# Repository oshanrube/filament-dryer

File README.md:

# Filament dryer

3D-printed filament dryer boxes, one per printer: heated to 40-70 °C, weighing the reel and reporting to the Printer Control Center over Wi-Fi. Two versions share the same heater, fans, controller, sensors and 12 V feed, so they use the same spares.

| Version | Folder | What it is |
| --- | --- | --- |
| 2-roll feeder | [`2-roll-feeder/`](2-roll-feeder/) | Two reels and a feeder pod; switches to the second reel automatically when the printer reports a runout |
| 1 roll | [`1-roll/`](1-roll/) | One reel, no feeders; smaller and simpler |
| Dumb (STC-3028) | [`dumb/`](dumb/) | The cheapest box: an STC-3028 humidity + temperature controller and a W1209 switch a 96 W heater in two steps. No microcontroller, scale or Wi-Fi |

**Published plan:** GitHub Pages from `/docs` on `main` (Settings → Pages → Deploy from a branch → `main`, `/docs`). The site has an overview page and one tab per version.

## Layout

| Path | What |
| --- | --- |
| `<version>/page.html` | That version's page content |
| `<version>/bom.csv` | Parts list with AliExpress search terms and approximate prices |
| `<version>/wiring.svg`, `<version>/wiring-table.html` | Wiring diagram and connector table (generated by `tools/gen_wiring.py`) |
| `<version>/images/` | Drawings (1-roll ones generated by `1-roll/tools/gen_drawings.py`) |
| `pcb/` | Controller board for JLCPCB assembly: wired schematic (`pcb/schematic.svg`/`.pdf`), KiCad schematic, JLCPCB BOMs (see `pcb/README.md`) |
| `firmware/` | ESP32-C3 firmware (PlatformIO, like the gate controller): build `dryer-1roll` runs the 1-roll PCB and the perfboard. See `firmware/README.md` |
| `.github/workflows/firmware.yml` | Builds the firmware on a `fw-v*` tag and attaches `dryer-1roll.bin` (OTA) and `dryer-1roll-full.bin` (flash at 0x0) to the release |
| `site/layout.html`, `site/overview.html` | Shared page shell with the tabs, and the overview page |
| `tools/build_site.py` | Builds `docs/` (the published site) from the folders above |
| `docs/` | Generated; don't edit by hand |

## Rebuild

```bash
python3 1-roll/tools/gen_drawings.py && python3 tools/gen_wiring.py && python3 dumb/tools/gen_dumb.py
```

```bash
python3 pcb/tools/gen_kicad.py && python3 pcb/tools/gen_schematic_svg.py && node pcb/tools/svg_to_pdf.js pcb/schematic.svg pcb/schematic.pdf
```

```bash
python3 tools/build_site.py
```

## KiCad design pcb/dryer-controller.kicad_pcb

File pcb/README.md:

# Dryer controller board (JLCPCB assembly)

One controller board for both dryer versions. The 2-roll build fits everything; the 1-roll build leaves the feeder parts off. KiCad 7 project, generated from one table in `tools/gen_kicad.py`.

| File | What |
| --- | --- |
| `schematic.svg`, `schematic.pdf` | The board with every wire drawn, for reading (from `tools/gen_schematic_svg.py`; PDF via `node tools/svg_to_pdf.js`) |
| `dryer-controller.kicad_sch` | Schematic (open in KiCad 7 or newer) |
| `dryer-controller.kicad_pcb` | Starting board: every footprint with its nets, linked to the schematic, placed in rows. Not laid out or routed yet, and no board outline |
| `libs/`, `fp-lib-table` | Every footprint the board uses, copied from KiCad 7, so the project opens without KiCad's libraries installed |
| `easyeda/dryer-controller-kicad.zip` | The whole project zipped the way KiCad's File → Archive Project packs it, for EasyEDA Pro's KiCad import |
| `dryer.kicad_sym` | Project symbols: ESP32-C3-WROOM-02, TMC2209-LA, UCC27517 (footprints all come from KiCad's own libraries) |
| `export/dryer-controller.pdf`, `.svg`, `.net` | Schematic PDF/SVG and netlist |
| `jlcpcb/bom-2-roll.csv`, `jlcpcb/bom-1-roll.csv` | JLCPCB assembly BOMs (Comment, Designator, Footprint, LCSC Part #) |

## Status

- **Done:** schematic and BOMs. Every LCSC number was checked on its JLCPCB page on 2026-11-24 (manufacturer part matches, all in stock). The exported netlist was checked pin by pin against the design table, and every symbol pin was checked against a pad in its footprint.
- **Not done yet:** PCB layout. JLCPCB also needs Gerbers and a placement (CPL) file, which come from the layout.

## What's on the board

| Block | Parts | Notes |
| --- | --- | --- |
| 12 V in | J1 XT60PW-M at the board edge, F1 ATO blade-fuse holder (fit a 15 A fuse), C1 100 µF, C2 | The supply lead ends in an XT60-F plug; J1 pokes through the base wall |
| 5 V buck | U2 AP63205WU-7, L1 4.7 µH, C3 10 µF, C5/C6 2×22 µF, C4 100 nF | Values from the AP63205 datasheet, Table 3 |
| Controller | U1 ESP32-C3-WROOM-02-N4 module (4 MB flash, PCB antenna), SW2 reset, SW3 boot, R16/C16 EN delay, R17 boot pull-up | R1-R3 4.7 k (1-wire, I2C), R4 1 k (motion signal) |
| USB and 3.3 V | J2 USB-C (data only, R18/R19 5.1 k on CC), U12 AMS1117-3.3, C12-C15 | Flash and logs over the C3's built-in USB; VBUS isn't connected |
| I/O expander | U3 MCP23017 | Lane sensors, BTT runout, button, buzzer, feeder EN/DIR |
| Heater switch | U4 UCC27517 gate driver, Q1 AOD4184A, R7 10 Ω, R8/R9 10 k | 12 V gate drive (see below) |
| Fans, buzzer | Q2-Q4 AO3400A, D1/D2 B5819W flyback diodes | Low-side switches |
| Scales | U7 (and U8 on the 2-roll) HX711, Q5/Q6 S8550, R20-R23, C17-C26 | Load cells plug straight into J11/J12; 4.3 V excitation |
| Bay sensor | U13 SHT40-BD1B (I2C 0x45), C38 | On the board, which sits in the bay; place it at an edge away from U2, U12, U10, U11 |
| Sensor boards | SB1: U14 SHT40-AD1B (0x44), C37, J18 pads. SB2: U15 DS18B20Z, C39, J19 pads | Small boards on break-off tabs; harness wires solder to their pads and plug into J5/J6 |
| Connectors | JST XH (J3-J17), TB2 heater | Same numbering as the wiring diagrams |
| Feeders (2-roll) | U10/U11 TMC2209-LA-T, C10/C11 100 µF, C27-C36, R24-R31, J16/J17 | Standalone, 1/8 step, about 0.72 A RMS |

**Heater switch:** the earlier plan drove an IRLB8721 straight from the ESP32's 3.3 V. At 12.5 A that runs too hot (roughly 15 mΩ at 3.3 V, about 2.3 W in a TO-220 without a heatsink). The board drives the AOD4184A (7 mΩ at 10 V) from a UCC27517 running on 12 V instead: about 1-1.6 W, spread into a copper pour under the TO-252 tab. The driver input has a pull-down, so the heater stays off while the ESP32 boots.

**Pin map:** the same as the 2-roll pin map in the docs. A 1-roll box built on this board uses it too: the BTT runout switch, button and buzzer go through the MCP23017, not straight to GPIO3, GPIO9 and GPIO10.

## Check before ordering

- [ ] **U1 antenna:** put the module's antenna end at (or over) the board edge, with no copper, parts or traces under it.
- [ ] **U10/U11 TMC2209:** the QFN footprint's exposed pad is 3.75 mm (the datasheet's nominal is 3.7 mm); tie it to a ground pour with the footprint's thermal vias. The pin numbers follow KiCad's own TMC2209-LA symbol (current library); check them against the datasheet's pin table once more before ordering.
- [ ] **Sensor boards SB1, SB2:** lay them out as small boards joined to the main board by mouse-bite tabs, so one order assembles everything; snap them off after delivery. Their nets (SB1_*, SB2_*) reach the main board only through the harness. JLCPCB may count break-off boards as extra designs in the panel: check the quote, or order them as a separate small board. Leave U14's top open to the air, and keep U13 away from the warm parts (a routed slot around it helps).
- [ ] **Motor current:** R24/R28 (39 k) and R25/R29 (10 k) set VREF to about 1.0 V, so about 0.72 A RMS (1.0 A peak) with the 0.11 Ω sense resistors. That suits the K1C extruder motor at feeding speeds; change R24/R28 to change it (I_RMS ≈ VREF / 2.5 V × 1.77 A).
- [ ] **Footprints to compare with the part drawings:** L1 uses the 4030 Changjiang footprint for the XR XRNR4030; TB2 uses the Phoenix MKDS 5.08 mm footprint for the KF128 terminal. **J1 polarity:** KiCad's XT60PW-M footprint marks pad 1 as − and pad 2 as +; check that against the Amass drawing and the lead before the first power-up. **F1:** the Littelfuse 178.6165 holder is specified for boards up to 1.5 mm thick; order 1.6 mm boards only after checking its pins still seat, or ask for 1.2 mm.
- [ ] **Layout rules for the 12.5 A path** (J1 → F1 → TB2 → Q1): wide pours, 2 oz copper, copper area under Q1.
- [ ] **Stock:** check again when ordering; MCP23017 (C47023) has had low stock at times.

## Opening it in EasyEDA Pro

EasyEDA Pro imports KiCad projects below version 10 (these files are KiCad 7). Its docs ask for a zip made by KiCad's own Archive Project, so that the libraries come along; `easyeda/dryer-controller-kicad.zip` is packed the same way.

1. In EasyEDA Pro, from the start page: File → Import → KiCad, and pick `easyeda/dryer-controller-kicad.zip`.
2. Check the schematic and that each part kept its LCSC number (the symbols carry `LCSC`, `Supplier` = LCSC and `Supplier Part` fields). Where a part lost its link, bind it to the LCSC number from `jlcpcb/bom-2-roll.csv`.
3. Open the PCB, draw the board outline and lay it out (the checks below still apply), then order from EasyEDA straight to JLCPCB.

This zip hasn't been through EasyEDA's importer yet, so check the result: EasyEDA's docs warn that copper areas are rebuilt on import and that conversions between tools can't be guaranteed.

## Ordering at JLCPCB

1. Lay out the PCB in KiCad (open `dryer-controller.kicad_sch`, then Tools → Update PCB from Schematic).
2. Export Gerbers, drill files and the placement (CPL) file.
3. Order PCB assembly and upload `jlcpcb/bom-2-roll.csv` (or `bom-1-roll.csv`) as the BOM. Every part on the board is in JLCPCB's library, so it arrives fully assembled. The JST, screw-terminal and buzzer parts are through-hole: keep them for JLCPCB's through-hole assembly, or remove those lines and solder them yourself.
4. One order uses one BOM. For a mix of 2-roll and 1-roll boxes, either order all boards with the 2-roll BOM (the unused feeder and second-scale parts do no harm) or place two orders.
5. Flash the first firmware over USB-C with the 12 V feed plugged in (hold BOOT, tap RESET if it doesn't enter download mode); updates after that go over Wi-Fi.

**Cost (checked on JLCPCB 2026-11-24):** parts about US$16 per 2-roll board and US$9 per 1-roll board, plus JLCPCB's US$3 fee per extended part type per order (16 types on the 2-roll BOM, so about US$48 per order), the PCB, and assembly setup. For 5 boards, roughly US$30-35 per 2-roll board.

## Regenerate

```bash
python3 pcb/tools/gen_kicad.py
```

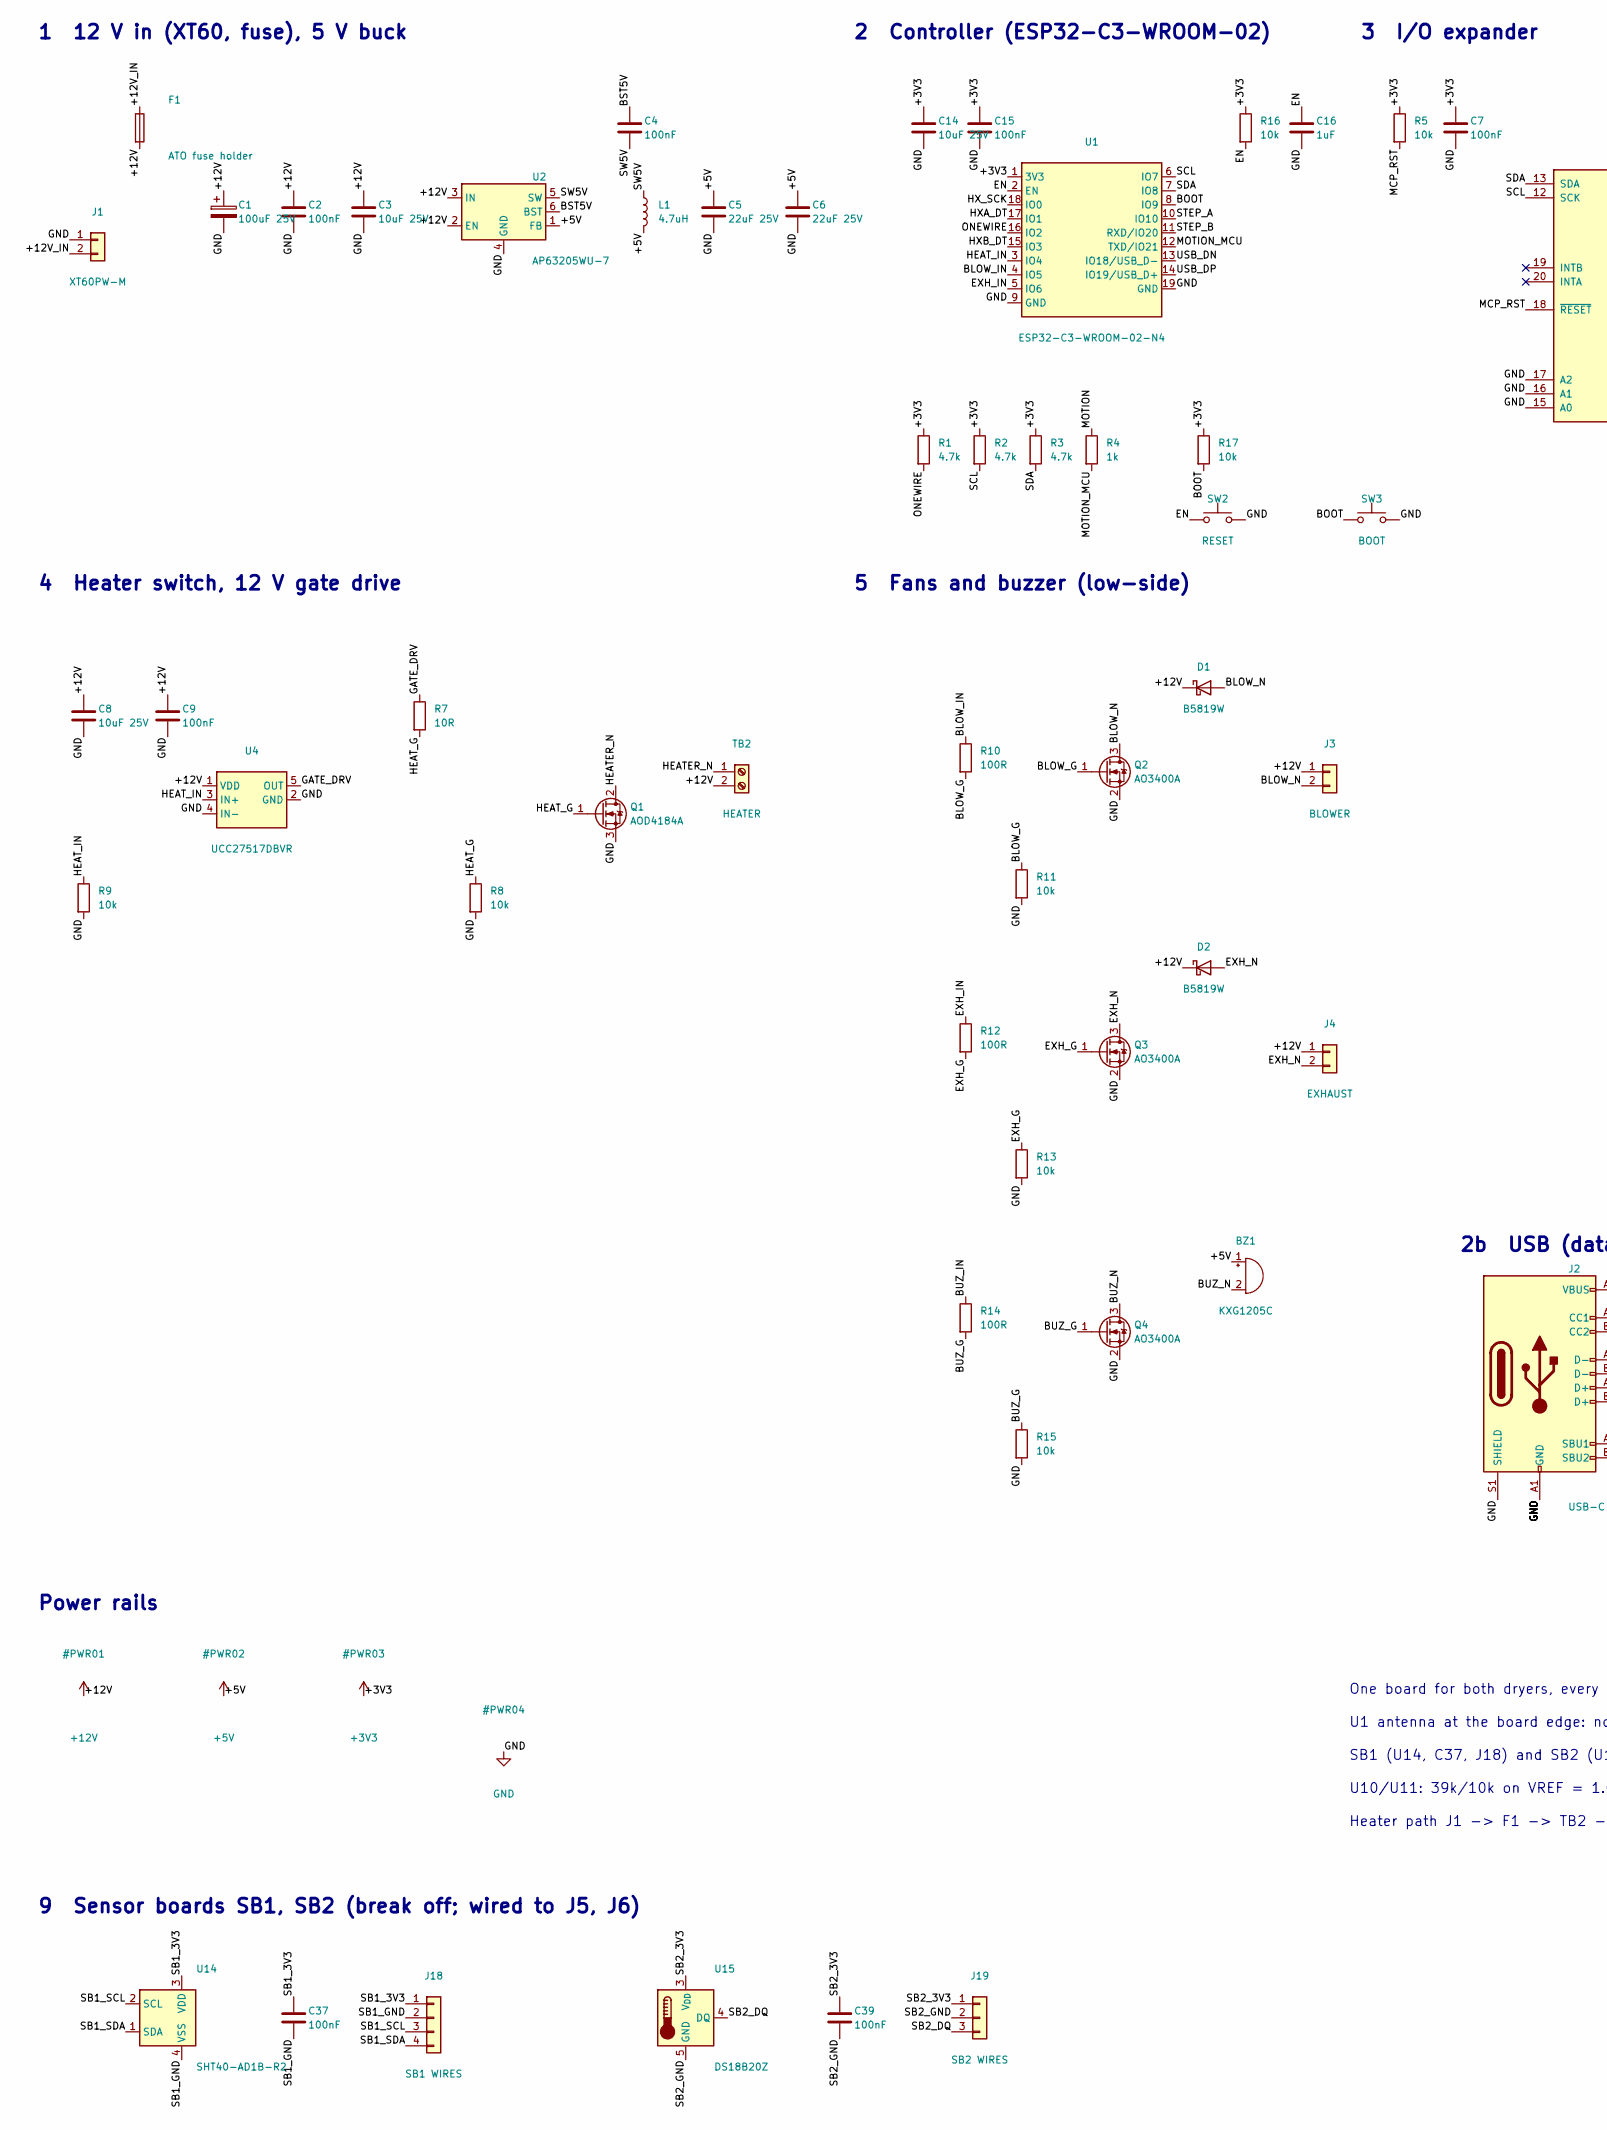
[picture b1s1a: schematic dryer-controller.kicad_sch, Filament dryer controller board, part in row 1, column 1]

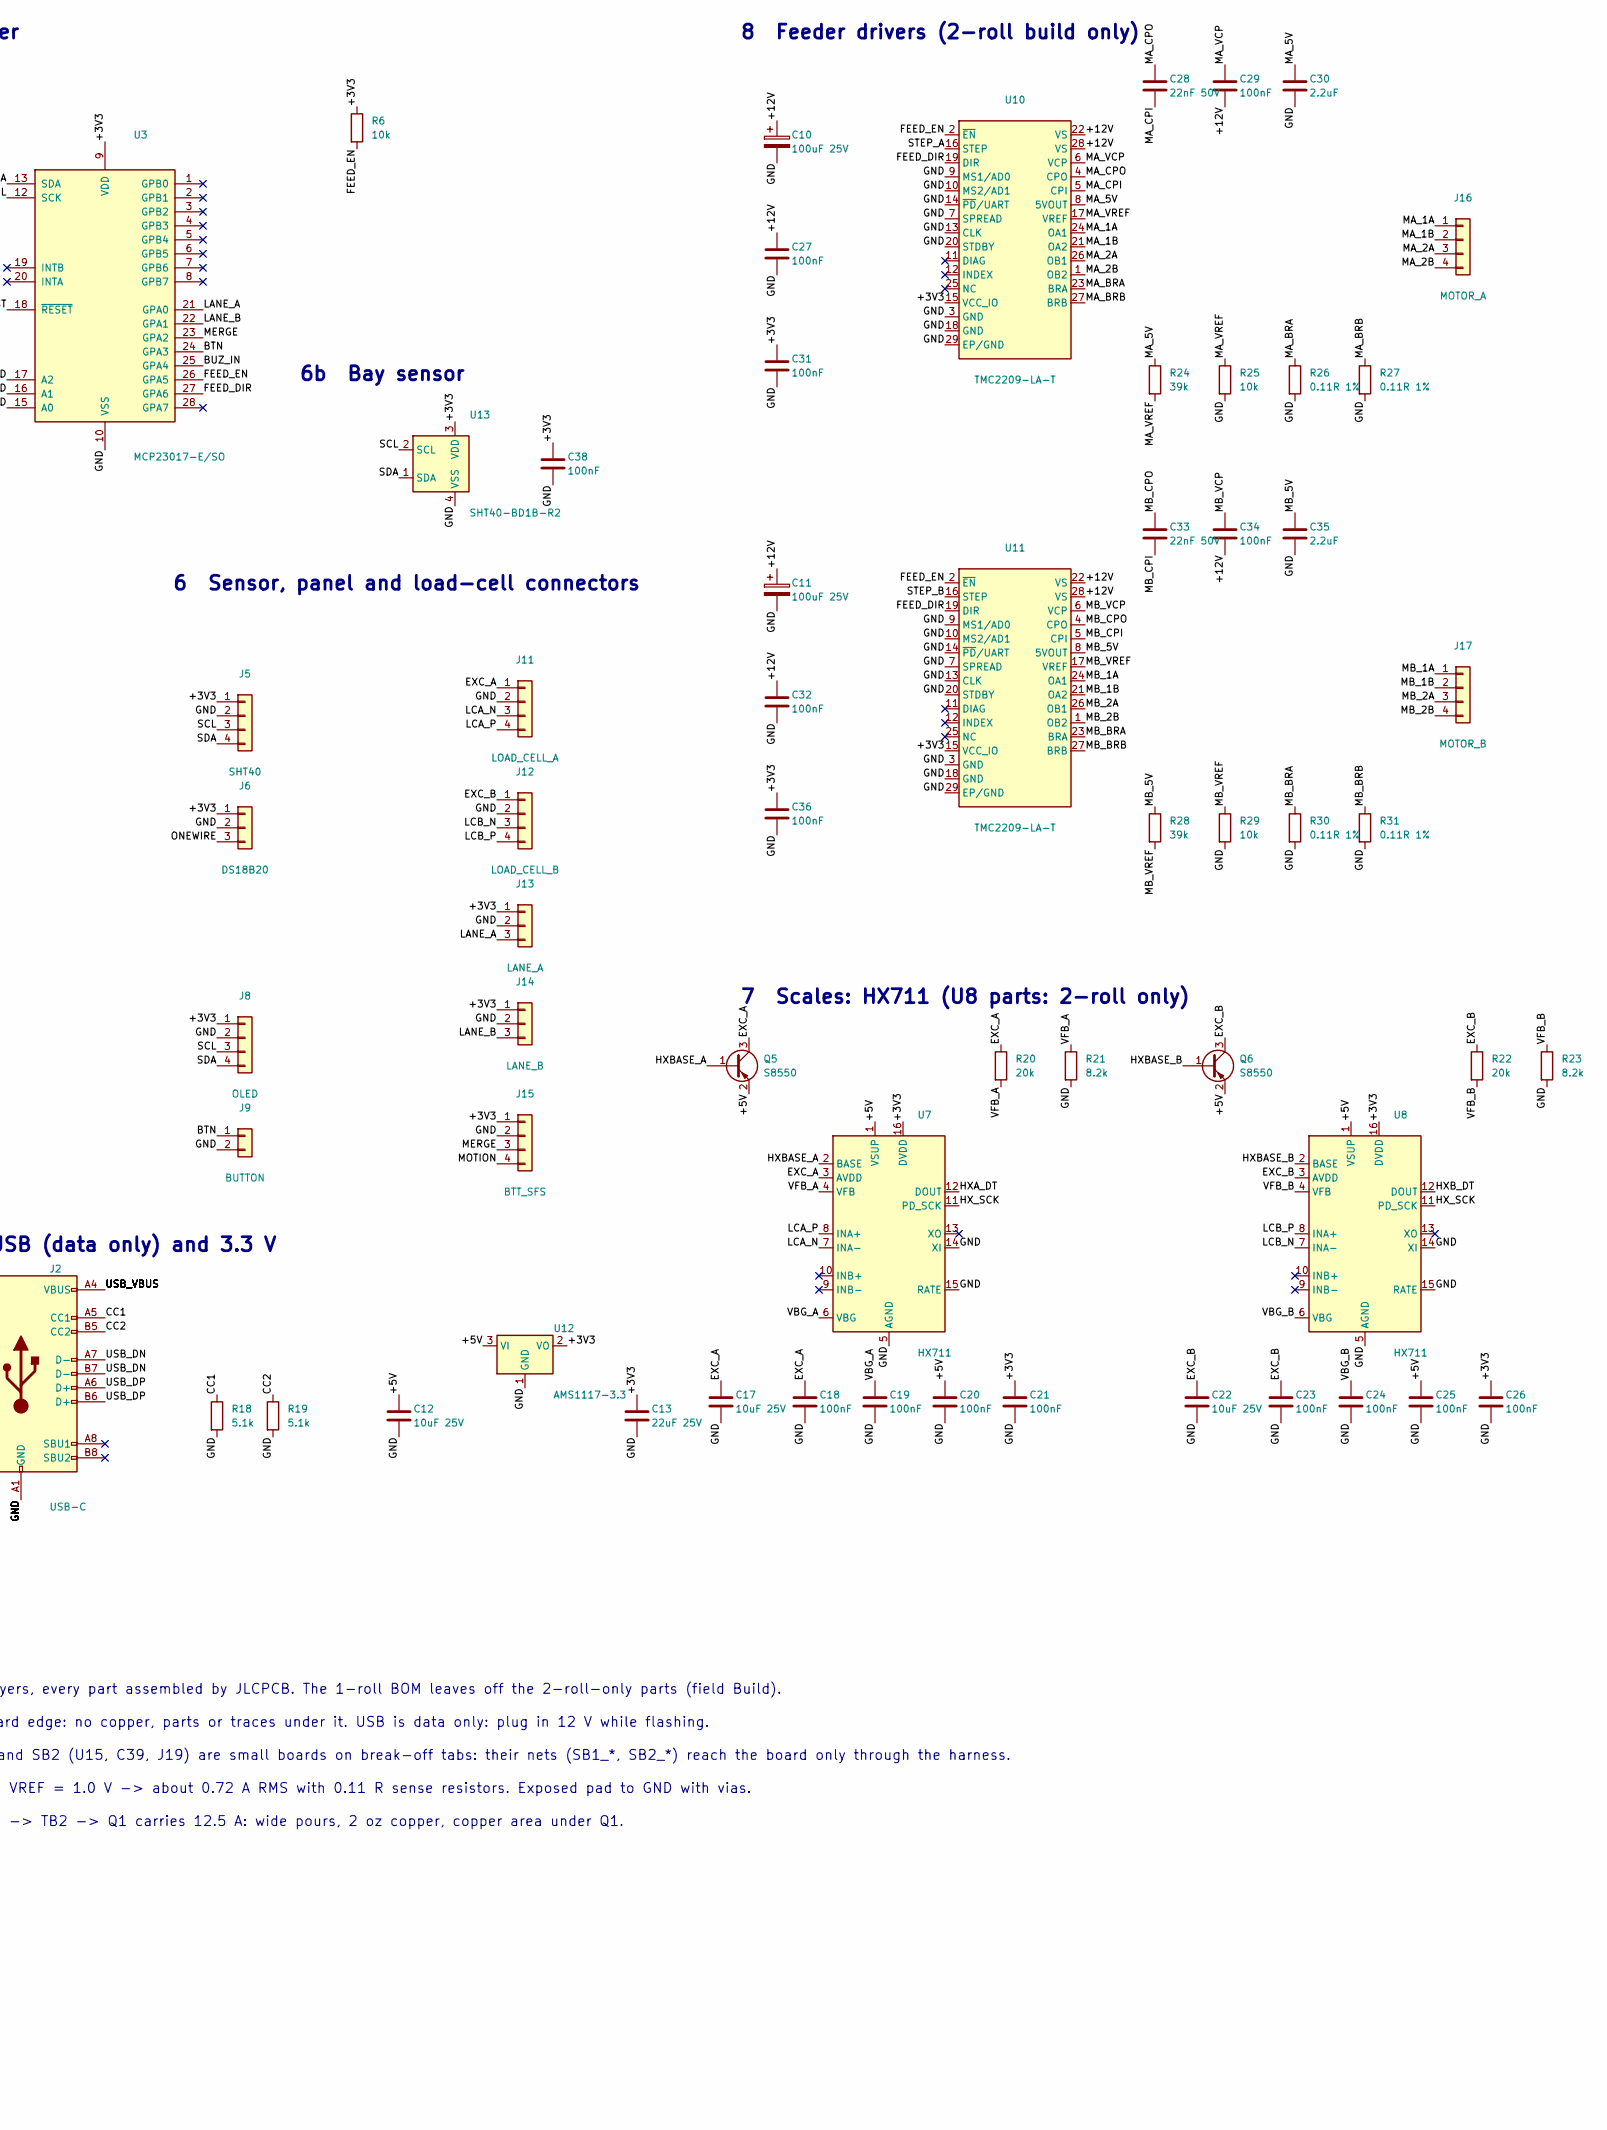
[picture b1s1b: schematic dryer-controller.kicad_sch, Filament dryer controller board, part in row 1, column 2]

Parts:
BZ1: KXG1205C; Buzzer_12x9.5RM7.6; MPN KXG1205C; LCSC C1122355
C1, C10, C11: 100uF 25V; CP_Elec_6.3x7.7; MPN EMVE250ARA101MF80G; LCSC C3008501
C2, C4, C7, C9, C15, C18, C19, C20, C21, C23, C24, C25, C26, C27, C29, C31, C32, C34, C36, C37, C38, C39: 100nF; C_0603_1608Metric; MPN CC0603KRX7R9BB104; LCSC C14663
C3, C8, C12, C14, C17, C22: 10uF 25V; C_0805_2012Metric; MPN CL21A106KAYNNNE; LCSC C15850
C5, C6, C13: 22uF 25V; C_0805_2012Metric; MPN CL21A226MAQNNNE; LCSC C45783
C16: 1uF; C_0603_1608Metric; MPN CL10A105KB8NNNC; LCSC C15849
C28, C33: 22nF 50V; C_0603_1608Metric; MPN CL10B223KB8NNNC; LCSC C21122
C30, C35: 2.2uF; C_0603_1608Metric; MPN CL10A225KO8NNNC; LCSC C23630
D1, D2: B5819W; D_SOD-123; MPN B5819W SL; LCSC C8598
F1: ATO fuse holder; FuseHolder_Blade_ATO_Littelfuse_FLR_178.6165; MPN 178.6165.0002; LCSC C207061
J1: XT60PW-M; AMASS_XT60PW-M_1x02_P7.20mm_Horizontal; MPN XT60PW-M; LCSC C98732
J2: USB-C; USB_C_Receptacle_HRO_TYPE-C-31-M-12; MPN TYPE-C-31-M-12; LCSC C165948
J3: BLOWER; JST_XH_B2B-XH-A_1x02_P2.50mm_Vertical; MPN B2B-XH-A(LF)(SN); LCSC C158012
J4: EXHAUST; JST_XH_B2B-XH-A_1x02_P2.50mm_Vertical; MPN B2B-XH-A(LF)(SN); LCSC C158012
J5: SHT40; JST_XH_B4B-XH-A_1x04_P2.50mm_Vertical; MPN B4B-XH-A(LF)(SN); LCSC C144395
J6: DS18B20; JST_XH_B3B-XH-A_1x03_P2.50mm_Vertical; MPN B3B-XH-A(LF)(SN); LCSC C144394
J8: OLED; JST_XH_B4B-XH-A_1x04_P2.50mm_Vertical; MPN B4B-XH-A(LF)(SN); LCSC C144395
J9: BUTTON; JST_XH_B2B-XH-A_1x02_P2.50mm_Vertical; MPN B2B-XH-A(LF)(SN); LCSC C158012
J11: LOAD_CELL_A; JST_XH_B4B-XH-A_1x04_P2.50mm_Vertical; MPN B4B-XH-A(LF)(SN); LCSC C144395
J12: LOAD_CELL_B; JST_XH_B4B-XH-A_1x04_P2.50mm_Vertical; MPN B4B-XH-A(LF)(SN); LCSC C144395
J13: LANE_A; JST_XH_B3B-XH-A_1x03_P2.50mm_Vertical; MPN B3B-XH-A(LF)(SN); LCSC C144394
J14: LANE_B; JST_XH_B3B-XH-A_1x03_P2.50mm_Vertical; MPN B3B-XH-A(LF)(SN); LCSC C144394
J15: BTT_SFS; JST_XH_B4B-XH-A_1x04_P2.50mm_Vertical; MPN B4B-XH-A(LF)(SN); LCSC C144395
J16: MOTOR_A; JST_XH_B4B-XH-A_1x04_P2.50mm_Vertical; MPN B4B-XH-A(LF)(SN); LCSC C144395
J17: MOTOR_B; JST_XH_B4B-XH-A_1x04_P2.50mm_Vertical; MPN B4B-XH-A(LF)(SN); LCSC C144395
J18: SB1 WIRES; PinHeader_1x04_P2.54mm_Vertical
J19: SB2 WIRES; PinHeader_1x03_P2.54mm_Vertical
L1: 4.7uH; L_Changjiang_FNR4030S; MPN XRNR4030-4.7uH/M; LCSC C5289366
Q1: AOD4184A; TO-252-2; MPN AOD4184A; LCSC C99124
Q2, Q3, Q4: AO3400A; SOT-23; MPN AO3400A; LCSC C20917
Q5, Q6: S8550; SOT-23; MPN S8550 (RANGE:120-200); LCSC C105432
R1, R2, R3: 4.7k; R_0603_1608Metric; MPN 0603WAF4701T5E; LCSC C23162
R4: 1k; R_0603_1608Metric; MPN 0603WAF1001T5E; LCSC C21190
R5, R6, R8, R9, R11, R13, R15, R16, R17, R25, R29: 10k; R_0603_1608Metric; MPN 0603WAF1002T5E; LCSC C25804
R7: 10R; R_0603_1608Metric; MPN 0603WAF100JT5E; LCSC C22859
R10, R12, R14: 100R; R_0603_1608Metric; MPN 0603WAF1000T5E; LCSC C22775
R18, R19: 5.1k; R_0603_1608Metric; MPN 0603WAF5101T5E; LCSC C23186
R20, R22: 20k; R_0603_1608Metric; MPN 0603WAF2002T5E; LCSC C4184
R21, R23: 8.2k; R_0603_1608Metric; MPN 0603WAF8201T5E; LCSC C25981
R24, R28: 39k; R_0603_1608Metric; MPN 0603WAF3902T5E; LCSC C23153
R26, R27, R30, R31: 0.11R 1%; R_1206_3216Metric; MPN 1206W4F110LT5E; LCSC C82532
SW2: RESET; SW_Push_1P1T_XKB_TS-1187A; MPN TS-1187A-B-A-B; LCSC C318884
SW3: BOOT; SW_Push_1P1T_XKB_TS-1187A; MPN TS-1187A-B-A-B; LCSC C318884
TB2: HEATER; TerminalBlock_Phoenix_MKDS-1,5-2-5.08_1x02_P5.08mm_Horizont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; MPN KF128-5.08-2P-AA; LCSC C474952
U1: ESP32-C3-WROOM-02-N4; ESP32-C3-WROOM-02; MPN ESP32-C3-WROOM-02-N4; LCSC C2934560
U2: AP63205WU-7; TSOT-23-6; MPN AP63205WU-7; LCSC C2071056
U3: MCP23017-E/SO; SOIC-28W_7.5x17.9mm_P1.27mm; MPN MCP23017-E/SO; LCSC C47023
U4: UCC27517DBVR; SOT-23-5; MPN UCC27517DBVR; LCSC C99395
U7, U8: HX711; SOP-16_3.9x9.9mm_P1.27mm; MPN HX711; LCSC C43656
U10, U11: TMC2209-LA-T; QFN-28-1EP_5x5mm_P0.5mm_EP3.75x3.75mm_ThermalVias; MPN TMC2209-LA-T; LCSC C2150710
U12: AMS1117-3.3; SOT-223-3_TabPin2; MPN AMS1117-3.3; LCSC C6186
U13: SHT40-BD1B-R2; Sensirion_DFN-4_1.5x1.5mm_P0.8mm_SHT4x_NoCentralPad; MPN SHT40-BD1B-R2; LCSC C7461849
U14: SHT40-AD1B-R2; Sensirion_DFN-4_1.5x1.5mm_P0.8mm_SHT4x_NoCentralPad; MPN SHT40-AD1B-R2; LCSC C2909890
U15: DS18B20Z; SOIC-8_3.9x4.9mm_P1.27mm; MPN DS18B20Z(UMW); LCSC C695837

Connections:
+3V3: C7.1, C13.1, C14.1, C15.1, C21.1, C26.1, C31.1, C36.1, C38.1, J5.1, J6.1, J8.1, J13.1, J14.1, J15.1, R1.1, R2.1, R3.1, R5.1, R6.1, R16.1, R17.1, U1.1 (3V3), U3.9 (VDD), U7.16 (DVDD), U8.16 (DVDD), U10.15 (VCC_IO), U11.15 (VCC_IO), U12.2 (VO), U13.3 (VDD)
+5V: BZ1.1 (+), C5.1, C6.1, C12.1, C20.1, C25.1, L1.2, Q5.2 (E), Q6.2 (E), U2.1 (FB), U7.1 (VSUP), U8.1 (VSUP), U12.3 (VI)
+12V: C1.1, C2.1, C3.1, C8.1, C9.1, C10.1, C11.1, C27.1, C29.2, C32.1, C34.2, D1.1 (K), D2.1 (K), F1.2, J3.1, J4.1, TB2.2, U2.2 (EN), U2.3 (IN), U4.1 (VDD), U10.22 (VS), U10.28 (VS), U11.22 (VS), U11.28 (VS)
/+12V_IN: F1.1, J1.2
/BLOW_G: Q2.1 (G), R10.2, R11.1
/BLOW_IN: R10.1, U1.4 (IO5)
/BLOW_N: D1.2 (A), J3.2, Q2.3 (D)
/BOOT: R17.2, SW3.1, U1.8 (IO9)
/BST5V: C4.1, U2.6 (BST)
/BTN: J9.1, U3.24 (GPA3)
/BUZ_G: Q4.1 (G), R14.2, R15.1
/BUZ_IN: R14.1, U3.25 (GPA4)
/BUZ_N: BZ1.2 (-), Q4.3 (D)
/CC1: J2.A5 (CC1), R18.1
/CC2: J2.B5 (CC2), R19.1
/EN: C16.1, R16.2, SW2.1, U1.2 (EN)
/EXC_A: C17.1, C18.1, J11.1, Q5.3 (C), R20.1, U7.3 (AVDD)
/EXC_B: C22.1, C23.1, J12.1, Q6.3 (C), R22.1, U8.3 (AVDD)
/EXH_G: Q3.1 (G), R12.2, R13.1
/EXH_IN: R12.1, U1.5 (IO6)
/EXH_N: D2.2 (A), J4.2, Q3.3 (D)
/FEED_DIR: U3.27 (GPA6), U10.19 (DIR), U11.19 (DIR)
/FEED_EN: R6.2, U3.26 (GPA5), U10.2 (~EN), U11.2 (~EN)
/GATE_DRV: R7.1, U4.5 (OUT)
/HEATER_N: Q1.2 (D), TB2.1
/HEAT_G: Q1.1 (G), R7.2, R8.1
/HEAT_IN: R9.1, U1.3 (IO4), U4.3 (IN+)
/HXA_DT: U1.17 (IO1), U7.12 (DOUT)
/HXBASE_A: Q5.1 (B), U7.2 (BASE)
/HXBASE_B: Q6.1 (B), U8.2 (BASE)
/HXB_DT: U1.15 (IO3), U8.12 (DOUT)
/HX_SCK: U1.18 (IO0), U7.11 (PD_SCK), U8.11 (PD_SCK)
/LANE_A: J13.3, U3.21 (GPA0)
/LANE_B: J14.3, U3.22 (GPA1)
/LCA_N: J11.3, U7.7 (INA-)
/LCA_P: J11.4, U7.8 (INA+)
/LCB_N: J12.3, U8.7 (INA-)
/LCB_P: J12.4, U8.8 (INA+)
/MA_1A: J16.1, U10.24 (OA1)
/MA_1B: J16.2, U10.21 (OA2)
/MA_2A: J16.3, U10.26 (OB1)
/MA_2B: J16.4, U10.1 (OB2)
/MA_5V: C30.1, R24.1, U10.8 (5VOUT)
/MA_BRA: R26.1, U10.23 (BRA)
/MA_BRB: R27.1, U10.27 (BRB)
/MA_CPI: C28.2, U10.5 (CPI)
/MA_CPO: C28.1, U10.4 (CPO)
/MA_VCP: C29.1, U10.6 (VCP)
/MA_VREF: R24.2, R25.1, U10.17 (VREF)
/MB_1A: J17.1, U11.24 (OA1)
/MB_1B: J17.2, U11.21 (OA2)
/MB_2A: J17.3, U11.26 (OB1)
/MB_2B: J17.4, U11.1 (OB2)
/MB_5V: C35.1, R28.1, U11.8 (5VOUT)
/MB_BRA: R30.1, U11.23 (BRA)
/MB_BRB: R31.1, U11.27 (BRB)
/MB_CPI: C33.2, U11.5 (CPI)
/MB_CPO: C33.1, U11.4 (CPO)
/MB_VCP: C34.1, U11.6 (VCP)
/MB_VREF: R28.2, R29.1, U11.17 (VREF)
/MCP_RST: R5.2, U3.18 (~RESET)
/MERGE: J15.3, U3.23 (GPA2)
/MOTION: J15.4, R4.1
/MOTION_MCU: R4.2, U1.12 (TXD/IO21)
/ONEWIRE: J6.3, R1.2, U1.16 (IO2)
/SB1_3V3: C37.1, J18.1, U14.3 (VDD)
/SB1_GND: C37.2, J18.2, U14.4 (VSS)
/SB1_SCL: J18.3, U14.2 (SCL)
/SB1_SDA: J18.4, U14.1 (SDA)
/SB2_3V3: C39.1, J19.1, U15.3 (V_{DD})
/SB2_DQ: J19.3, U15.4 (DQ)
/SB2_GND: C39.2, J19.2, U15.5 (GND)
/SCL: J5.3, J8.3, R2.2, U1.6 (IO7), U3.12 (SCK), U13.2 (SCL)
/SDA: J5.4, J8.4, R3.2, U1.7 (IO8), U3.13 (SDA), U13.1 (SDA)
/STEP_A: U1.10 (IO10), U10.16 (STEP)
/STEP_B: U1.11 (RXD/IO20), U11.16 (STEP)
/SW5V: C4.2, L1.1, U2.5 (SW)
/USB_DN: J2.A7 (D-), J2.B7 (D-), U1.13 (IO18/USB_D-)
/USB_DP: J2.A6 (D+), J2.B6 (D+), U1.14 (IO19/USB_D+)
/USB_VBUS: J2.A4 (VBUS), J2.A9 (VBUS), J2.B4 (VBUS), J2.B9 (VBUS)
/VBG_A: C19.1, U7.6 (VBG)
/VBG_B: C24.1, U8.6 (VBG)
/VFB_A: R20.2, R21.1, U7.4 (VFB)
/VFB_B: R22.2, R23.1, U8.4 (VFB)
GND: C1.2, C2.2, C3.2, C5.2, C6.2, C7.2, C8.2, C9.2, C10.2, C11.2, C12.2, C13.2, C14.2, C15.2, C16.2, C17.2, C18.2, C19.2, C20.2, C21.2, C22.2, C23.2, C24.2, C25.2, C26.2, C27.2, C30.2, C31.2, C32.2, C35.2, C36.2, C38.2, J1.1, J2.A1 (GND), J2.A12 (GND), J2.B1 (GND), J2.B12 (GND), J2.S1 (SHIELD), J5.2, J6.2, J8.2, J9.2, J11.2, J12.2, J13.2, J14.2, J15.2, Q1.3 (S), Q2.2 (S), Q3.2 (S), Q4.2 (S), R8.2, R9.2, R11.2, R13.2, R15.2, R18.2, R19.2, R21.2, R23.2, R25.2, R26.2, R27.2, R29.2, R30.2, R31.2, SW2.2, SW3.2, U1.9 (GND), U1.19 (GND), U2.4 (GND), U3.10 (VSS), U3.15 (A0), U3.16 (A1), U3.17 (A2), U4.2 (GND), U4.4 (IN-), U7.5 (AGND), U7.14 (XI), U7.15 (RATE), U8.5 (AGND), U8.14 (XI), U8.15 (RATE), U10.3 (GND), U10.7 (SPREAD), U10.9 (MS1/AD0), U10.10 (MS2/AD1), U10.13 (CLK), U10.14 (~PD/UART), U10.18 (GND), U10.20 (STDBY), U10.29 (EP/GND), U11.3 (GND), U11.7 (SPREAD), U11.9 (MS1/AD0), U11.10 (MS2/AD1), U11.13 (CLK), U11.14 (~PD/UART), U11.18 (GND), U11.20 (STDBY), U11.29 (EP/GND), U12.1 (GND), U13.4 (VSS)

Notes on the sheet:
1 12 V in (XT60, fuse), 5 V buck
2 Controller (ESP32-C3-WROOM-02)
3 I/O expander
4 Heater switch, 12 V gate drive
5 Fans and buzzer (low-side)
6 Sensor, panel and load-cell connectors
7 Scales: HX711 (U8 parts: 2-roll only)
8 Feeder drivers (2-roll build only)
2b USB (data only) and 3.3 V
9 Sensor boards SB1, SB2 (break off; wired to J5, J6)
6b Bay sensor
Power rails
One board for both dryers, every part assembled by JLCPCB. The 1-roll BOM leaves off the 2-roll-only parts (field Build).
U1 antenna at the board edge: no copper, parts or traces under it. USB is data only: plug in 12 V while flashing.
SB1 (U14, C37, J18) and SB2 (U15, C39, J19) are small boards on break-off tabs: their nets (SB1_*, SB2_*) reach the board only through the harness.
U10/U11: 39k/10k on VREF = 1.0 V -> about 0.72 A RMS with 0.11 R sense resistors. Exposed pad to GND with vias.
Heater path J1 -> F1 -> TB2 -> Q1 carries 12.5 A: wide pours, 2 oz copper, copper area under Q1.

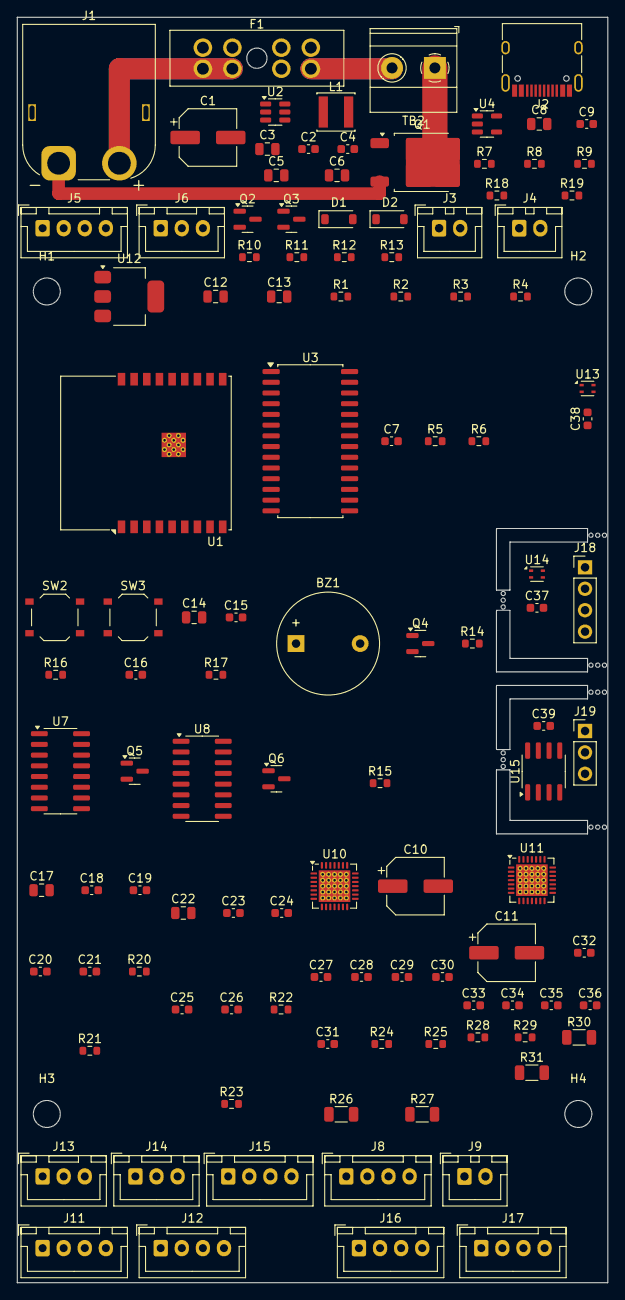
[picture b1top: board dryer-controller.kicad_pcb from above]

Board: 2 copper layers, 70.0 x 150.0 mm, 123 parts (0 on the bottom side), 85 nets.

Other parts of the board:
H1, H2, H3, H4: M3; MountingHole_3.2mm_M3
MB1, MB2, MB3, MB4, MB5, MB6: mouse bites

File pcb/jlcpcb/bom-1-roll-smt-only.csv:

Comment,Designator,Footprint,LCSC Part #,Qty,MPN,Note
100uF 25V,C1,CP_Elec_6.3x7.7,C3008501,1,EMVE250ARA101MF80G,
1uF,C16,C_0603_1608Metric,C15849,1,CL10A105KB8NNNC,
100nF,"C2,C4,C7,C9,C15,C18,C19,C20,C21,C37,C38,C39",C_0603_1608Metric,C14663,12,CC0603KRX7R9BB104,
10uF 25V,"C3,C8,C12,C14,C17",C_0805_2012Metric,C15850,5,CL21A106KAYNNNE,
22uF 25V,"C5,C6,C13",C_0805_2012Metric,C45783,3,CL21A226MAQNNNE,
B5819W,"D1,D2",D_SOD-123,C8598,2,B5819W SL,
USB-C,J2,USB_C_Receptacle_HRO_TYPE-C-31-M-12,C165948,1,TYPE-C-31-M-12,"Programming and logs (USB serial/JTAG). Data only: VBUS is not connected, so plug in 12 V while flashing"
4.7uH,L1,L_Changjiang_FNR4030S,C5289366,1,XRNR4030-4.7uH/M,4x4 mm; check pads against the XRNR4030 drawing
AOD4184A,Q1,TO-252-2,C99124,1,AOD4184A,"12.5 A heater: big copper pour on the drain tab, 2 oz copper"
S8550,Q5,SOT-23,C105432,1,S8550 (RANGE:120-200),Excitation regulator pass transistor (AVDD = 4.3 V)
AO3400A,"Q2,Q3,Q4",SOT-23,C20917,3,AO3400A,
20k,R20,R_0603_1608Metric,C4184,1,0603WAF2002T5E,
8.2k,R21,R_0603_1608Metric,C25981,1,0603WAF8201T5E,
1k,R4,R_0603_1608Metric,C21190,1,0603WAF1001T5E,
10R,R7,R_0603_1608Metric,C22859,1,0603WAF100JT5E,
4.7k,"R1,R2,R3",R_0603_1608Metric,C23162,3,0603WAF4701T5E,
100R,"R10,R12,R14",R_0603_1608Metric,C22775,3,0603WAF1000T5E,
5.1k,"R18,R19",R_0603_1608Metric,C23186,2,0603WAF5101T5E,
10k,"R5,R6,R8,R9,R11,R13,R15,R16,R17",R_0603_1608Metric,C25804,9,0603WAF1002T5E,
TS-1187A-B-A-B,"SW2,SW3",SW_Push_1P1T_XKB_TS-1187A,C318884,2,TS-1187A-B-A-B,
ESP32-C3-WROOM-02-N4,U1,ESP32-C3-WROOM-02,C2934560,1,ESP32-C3-WROOM-02-N4,"Antenna end at the board edge, no copper under the antenna"
AMS1117-3.3,U12,SOT-223-3_TabPin2,C6186,1,AMS1117-3.3,"3.3 V for the module, MCP23017, sensors and logic (up to ~0.4 A peak)"
SHT40-BD1B-R2,U13,Sensirion_DFN-4_1.5x1.5mm_P0.8mm_SHT4x_NoCentralPad,C7461849,1,SHT40-BD1B-R2,"Bay sensor, address 0x45: place at a board edge away from U2, U12, U10, U11, with a slot around it"
SHT40-AD1B-R2,U14,Sensirion_DFN-4_1.5x1.5mm_P0.8mm_SHT4x_NoCentralPad,C2909890,1,SHT40-AD1B-R2,"Sensor board SB1 (chamber air), address 0x44"
DS18B20Z,U15,SOIC-8_3.9x4.9mm_P1.27mm,C695837,1,DS18B20Z(UMW),Sensor board SB2 (heater outlet air)
AP63205WU-7,U2,TSOT-23-6,C2071056,1,AP63205WU-7,
MCP23017-E/SO,U3,SOIC-28W_7.5x17.9mm_P1.27mm,C47023,1,MCP23017-E/SO,
UCC27517DBVR,U4,SOT-23-5,C99395,1,UCC27517DBVR,
HX711,U7,SOP-16_3.9x9.9mm_P1.27mm,C43656,1,HX711,"Load-cell ADC; 10 samples/s, internal oscillator"

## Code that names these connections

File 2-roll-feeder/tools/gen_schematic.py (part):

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# ---------------------------------------------------------------- frame
out.append(f"<rect width='{W}' height='{H}' fill='white'/>")
t(30, 44, "Two-reel filament dryer: schematic", 22, weight="bold")
t(30, 68, "ESP32-C3 SuperMini + MCP23017 · 12 V feed · K1C feeders and runout sensors · BTT motion sensor · nets with the same label are connected · rev 2026-11-23", 12.5, fill=QUIET)

# ---------------------------------------------------------------- power
section(20, 90, 520, 310, "1  Power in")
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# ---------------------------------------------------------------- MCU
section(560, 90, 520, 440, "2  Controller")
chip(740, 150, 170, "U1", "ESP32-C3 SuperMini",
     left=[("5V", "+5V"), ("GND", "GND"), ("3V3", "+3V3"), ("GPIO0", "HX_SCK"), ("GPIO1", "HXA_DT"),
           ("GPIO2", "ONEWIRE"), ("GPIO3", "HXB_DT"), ("GPIO4", "HEAT_G")],
     right=[("GPIO5", "BLOW_G"), ("GPIO6", "EXH_G"), ("GPIO7", "SCL"), ("GPIO8", "SDA"), ("GPIO9", None),
            ("GPIO10", "STEP_A"), ("GPIO20", "STEP_B"), ("GPIO21", None)],
     pitch=30, sub="on-board 3V3 regulator")
line(944, 388, 952, 388); resistor(952, 388, "R12 1k", vertical=False); line(982, 388, 992, 388); net(992, 388, "MOTION")
# pull-ups near MCU
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
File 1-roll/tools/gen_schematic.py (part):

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# ---------------------------------------------------------------- frame
out.append(f"<rect width='{W}' height='{H}' fill='white'/>")
t(30, 44, "Single-reel filament dryer: schematic", 22, weight="bold")
t(30, 68, "ESP32-C3 SuperMini · 12 V feed · BTT motion sensor · nets with the same label are connected · rev 2026-11-23", 12.5, fill=QUIET)

# ---------------------------------------------------------------- power
section(20, 90, 520, 310, "1  Power in")
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# ---------------------------------------------------------------- MCU
section(560, 90, 520, 440, "2  Controller")
chip(740, 150, 170, "U1", "ESP32-C3 SuperMini",
     left=[("5V", "+5V"), ("GND", "GND"), ("3V3", "+3V3"), ("GPIO0", "HX_SCK"), ("GPIO1", "HX_DT"),
           ("GPIO2", "ONEWIRE"), ("GPIO3", "RUNOUT"), ("GPIO4", "HEAT_G")],
     right=[("GPIO5", "BLOW_G"), ("GPIO6", "EXH_G"), ("GPIO7", "SCL"), ("GPIO8", "SDA"), ("GPIO9", "BTN"),
            ("GPIO10", "BUZ_G"), ("GPIO20", None), ("GPIO21", None)],
     pitch=30, sub="on-board 3V3 regulator")
line(944, 388, 952, 388); resistor(952, 388, "R12 1k", vertical=False); line(982, 388, 992, 388); net(992, 388, "MOTION")
# pull-ups near MCU
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chip(1300, 620, 140, "U13", "BTT SFS V2", left=[("VCC", "+3V3"), ("GND", "GND"), ("RUNOUT", "RUNOUT"), ("MOTION", "MOTION")], sub="at the filament exit")
chip(1300, 830, 140, "SW1", "Push button", left=[("1", "BTN"), ("2", "GND")], sub="panel, momentary")
t(1130, 960, "RUNOUT and BTN use the ESP32's internal pull-ups.", 10.5, fill=QUIET)
t(1130, 976, "BTN shares GPIO9 with BOOT: holding it at power-on", 10.5, fill=QUIET)
t(1130, 992, "enters flashing mode.", 10.5, fill=QUIET)

svg = (f"<svg xmlns='http://www.w3.org/2000/svg' viewBox='0 0 {W} {H}' width='{W}' height='{H}' {FONT}>"
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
